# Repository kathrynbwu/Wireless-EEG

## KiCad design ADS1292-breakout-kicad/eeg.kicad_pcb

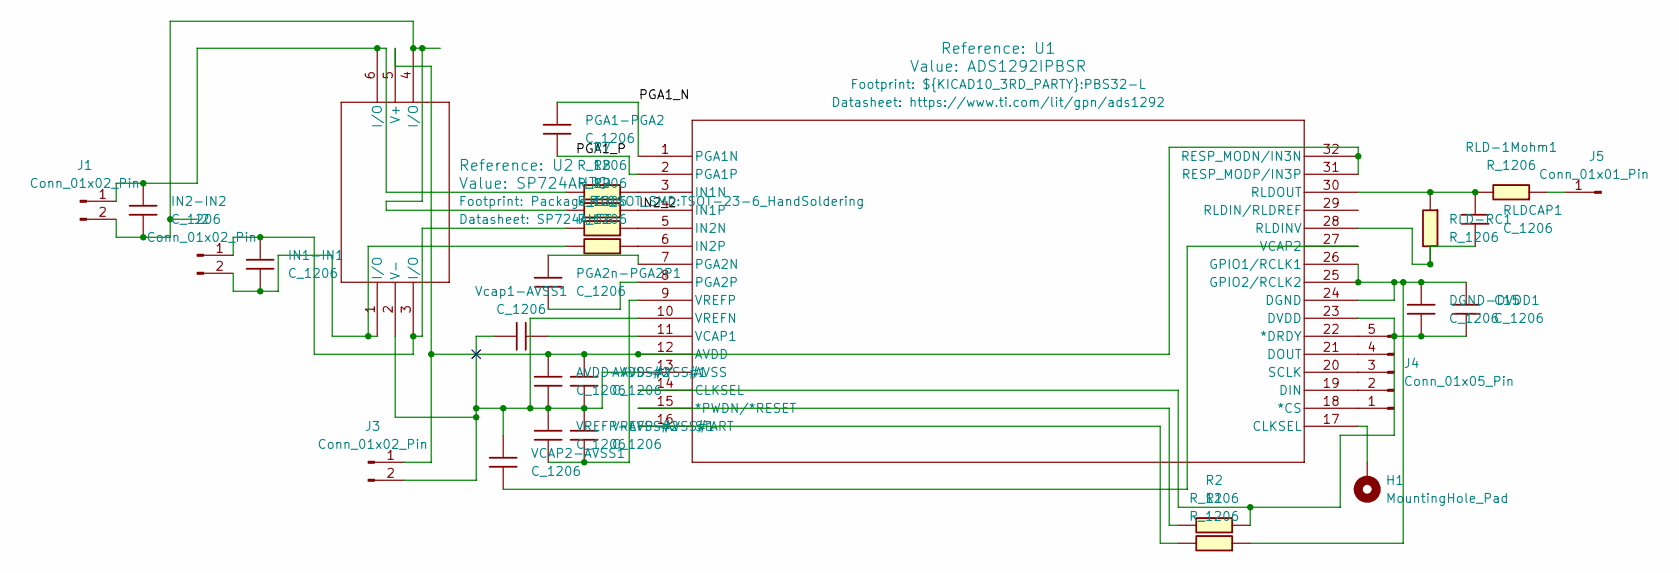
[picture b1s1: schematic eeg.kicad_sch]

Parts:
AVDD-AVSS#1, AVDD-AVSS#2: C_1206; C_0603_1608Metric
C15: C_1206; C_0603_1608Metric
DGND-DVDD1: C_1206; C_0603_1608Metric
H1: MountingHole_Pad; MountingHole_2.2mm_M2_ISO7380_Pad
IN1-IN1, IN2-IN2: C_1206; C_0603_1608Metric
J1, J2, J3: Conn_01x02_Pin; PinHeader_1x02_P2.54mm_Vertical
J4: Conn_01x05_Pin; PinSocket_1x05_P2.54mm_Vertical
J5: Conn_01x01_Pin; PinSocket_1x01_P2.54mm_Vertical
PGA1-PGA2, PGA2n-PGA2P1: C_1206; C_0603_1608Metric
R1, R2, R7, R8, R9, R10: R_1206; R_0603
RLD-1Mohm1: R_1206; R_0603
RLD-RC1: R_1206; R_0603
RLDCAP1: C_1206; C_0603_1608Metric
U1: ADS1292IPBSR; PBS32-L
U2: SP724AHTG; TSOT-23-6_HandSoldering
VCAP2-AVSS1: C_1206; C_0603_1608Metric
VREFP-AVSS#1, VREFP-AVSS#2: C_1206; C_0603_1608Metric
Vcap1-AVSS1: C_1206; C_0603_1608Metric

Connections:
/IN2_2: R8.2, U1.4 (IN1P)
/PGA1_N: PGA1-PGA2.1, U1.1 (PGA1N)
/PGA1_P: PGA1-PGA2.2, U1.2 (PGA1P)
unnamed: H1.1 (1_1), U1.17 (CLKSEL)
unnamed: IN2-IN2.2, J1.1, R7.1, U2.6 (I/O)
unnamed: IN2-IN2.1, J1.2, R8.1, U2.4 (I/O)
unnamed: IN1-IN1.1, J2.1, R9.1, U2.3 (I/O)
unnamed: IN1-IN1.2, J2.2, R10.1, U2.1 (I/O)
unnamed: AVDD-AVSS#1.1, AVDD-AVSS#2.1, J3.1, U1.12 (AVDD), U1.31 (RESP_MODP/IN3P), U1.32 (RESP_MODN/IN3N), U2.5 (V+)
unnamed: AVDD-AVSS#1.2, AVDD-AVSS#2.2, J3.2, U1.10 (VREFN), U1.13 (AVSS), U2.2 (V-), VCAP2-AVSS1.1, VREFP-AVSS#1.1, VREFP-AVSS#2.1, Vcap1-AVSS1.1
unnamed: J4.1, U1.18 (*CS)
unnamed: J4.2, U1.19 (DIN)
unnamed: J4.3, U1.20 (SCLK)
unnamed: J4.4, U1.21 (DOUT)
unnamed: J4.5, U1.22 (*DRDY)
unnamed: J5.1 (Pin_1_1), RLD-1Mohm1.2
unnamed: R2.1, U1.15 (*PWDN/*RESET)
unnamed: C15.1, DGND-DVDD1.1, R1.2, U1.24 (DGND), U1.25 (GPIO2/RCLK2), U1.26 (GPIO1/RCLK1)
unnamed: C15.2, DGND-DVDD1.2, R2.2, U1.14 (CLKSEL), U1.23 (DVDD)
unnamed: R7.2, U1.3 (IN1N)
unnamed: R9.2, U1.5 (IN2N)
unnamed: R10.2, U1.6 (IN2P)
unnamed: PGA2n-PGA2P1.1, U1.7 (PGA2N)
unnamed: PGA2n-PGA2P1.2, U1.8 (PGA2P)
unnamed: RLD-RC1.1, RLDCAP1.2, U1.28 (RLDINV)
unnamed: RLD-1Mohm1.1, RLD-RC1.2, RLDCAP1.1, U1.30 (RLDOUT)
unnamed: R1.1, U1.16 (START)
unnamed: U1.11 (VCAP1), Vcap1-AVSS1.2
unnamed: U1.27 (VCAP2), VCAP2-AVSS1.2
unnamed: U1.9 (VREFP), VREFP-AVSS#1.2, VREFP-AVSS#2.2

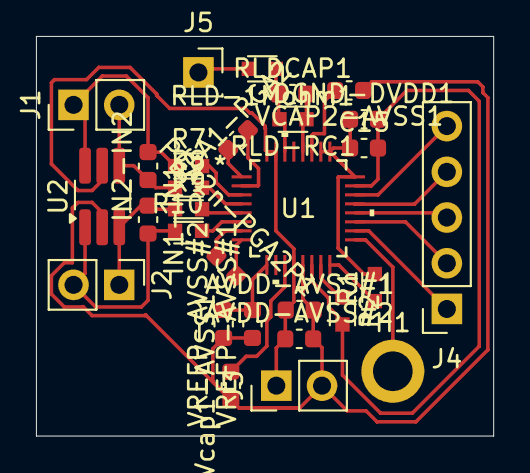
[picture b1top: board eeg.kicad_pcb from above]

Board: 2 copper layers, 25.4 x 22.2 mm, 29 parts (0 on the bottom side), 30 nets.
